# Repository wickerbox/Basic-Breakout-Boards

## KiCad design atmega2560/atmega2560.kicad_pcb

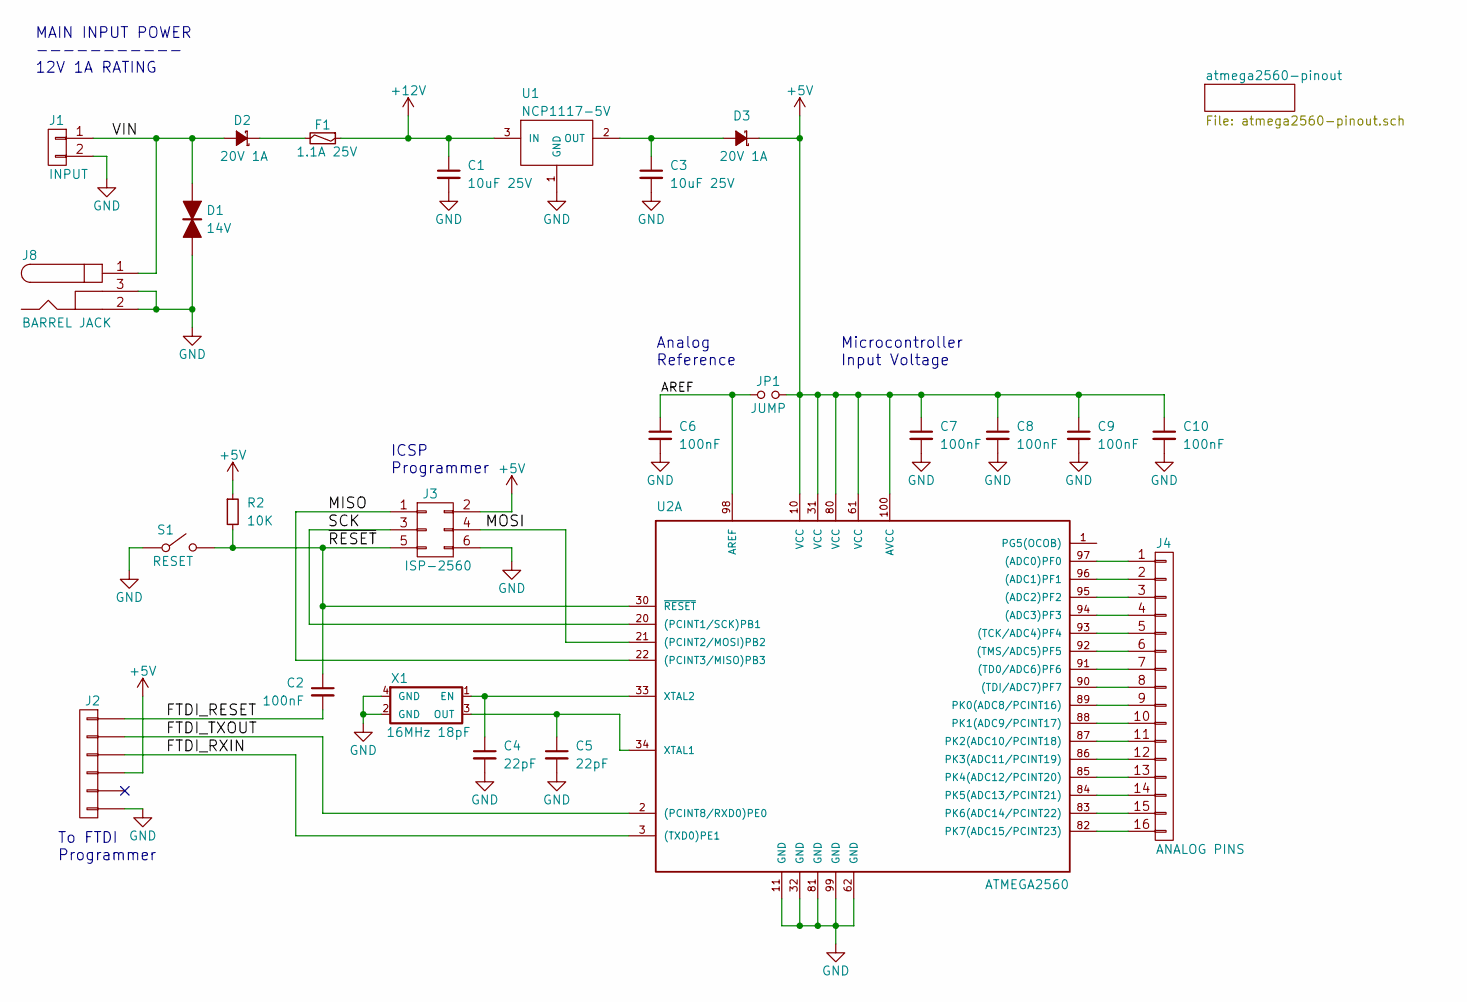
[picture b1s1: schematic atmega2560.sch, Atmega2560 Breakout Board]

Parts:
C1, C3: 10uF 25V; RLC-1210-SMD
C2, C6, C7, C8, C9, C10: 100nF; RLC-0603-SMD
C4, C5: 22pF; RLC-0603-SMD
D1: 14V; DIODE-SMA
D2, D3: 20V 1A; DIODE-SMA
F1: 1.1A 25V; RLC-1812-SMD
J1: INPUT; CONN-ONSHORE-SCREW-GREEN-2PIN-TH
J2: FTDI; CONN-HEADER-STRAIGHT-P2.54MM-1x06
J3: ISP-2560; CONN-HEADER-STRAIGHT-P2.54MM-2x03
J4: ANALOG PINS; CONN-HEADER-STRAIGHT-P2.54MM-1x16
J8: BARREL JACK; CONN-BARREL-JACK-2.5x5.5MM-TH
JP1: JUMP; CONN-HEADER-STRAIGHT-P2.54MM-1x02
R2: 10K; RLC-0805-SMD
S1: RESET; SWITCH-OMRON-MOMENTARY-SMD-B3U-1000P
U1: NCP1117-5V; DPAK
U2: ATMEGA2560; TQFP-100-14x14MM-P0.5MM
X1: 16MHz 18pF; CRYSTAL-CTS-4SMD

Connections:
+5V: C7.1, C8.1, C9.1, C10.1, D3.1 (K), J2.4, J3.2, JP1.2, R2.1, U2.10 (VCC), U2.31 (VCC), U2.61 (VCC), U2.80 (VCC), U2.100 (AVCC)
+12V: C1.1, F1.1, U1.3 (IN)
/AREF: C6.1, JP1.1, U2.98 (AREF)
/FTDI_RESET: C2.2, J2.1
/FTDI_RXIN: J2.3, U2.3 ((TXD0)PE1)
/FTDI_TXOUT: J2.2, U2.2 ((PCINT8/RXD0)PE0)
/MISO: J3.1, U2.22 ((PCINT3/MISO)PB3)
/MOSI: J3.4, U2.21 ((PCINT2/MOSI)PB2)
/SCK: J3.3, U2.20 ((PCINT1/SCK)PB1)
/VIN: D1.1, D2.2 (A), J1.1, J8.1
/~RESET: C2.1, J3.5, R2.2, S1.2, U2.30 (~RESET)
GND: C1.2, C3.2, C4.2, C5.2, C6.2, C7.2, C8.2, C9.2, C10.2, D1.2, J1.2, J2.6, J3.6, J8.2, J8.3, S1.1, U1.1 (GND), U2.11 (GND), U2.32 (GND), U2.62 (GND), U2.81 (GND), U2.99 (GND), X1.2 (GND), X1.4 (GND); also elsewhere on the board
unnamed: C3.1, D3.2 (A), U1.2 (OUT)
unnamed: C4.1, U2.33 (XTAL2), X1.1 (EN)
unnamed: C5.1, U2.34 (XTAL1), X1.3 (OUT)
unnamed: D2.1 (K), F1.2
unnamed: J4.1, U2.97 ((ADC0)PF0)
unnamed: J4.2, U2.96 ((ADC1)PF1)
unnamed: J4.3, U2.95 ((ADC2)PF2)
unnamed: J4.4, U2.94 ((ADC3)PF3)
unnamed: J4.5, U2.93 ((TCK/ADC4)PF4)
unnamed: J4.6, U2.92 ((TMS/ADC5)PF5)
unnamed: J4.7, U2.91 ((TD0/ADC6)PF6)
unnamed: J4.8, U2.90 ((TDI/ADC7)PF7)
unnamed: J4.9, U2.89 (PK0(ADC8/PCINT16))
unnamed: J4.10, U2.88 (PK1(ADC9/PCINT17))
unnamed: J4.11, U2.87 (PK2(ADC10/PCINT18))
unnamed: J4.12, U2.86 (PK3(ADC11/PCINT19))
unnamed: J4.13, U2.85 (PK4(ADC12/PCINT20))
unnamed: J4.14, U2.84 (PK5(ADC13/PCINT21))
unnamed: J4.15, U2.83 (PK6(ADC14/PCINT22))
unnamed: J4.16, U2.82 (PK7(ADC15/PCINT23))
unnamed 47: U2.1 (PG5(OCOB)); also elsewhere on the board

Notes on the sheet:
MAIN INPUT POWER ----------- 12V 1A RATING
To FTDI Programmer
ICSP Programmer
Analog Reference
Microcontroller Input Voltage

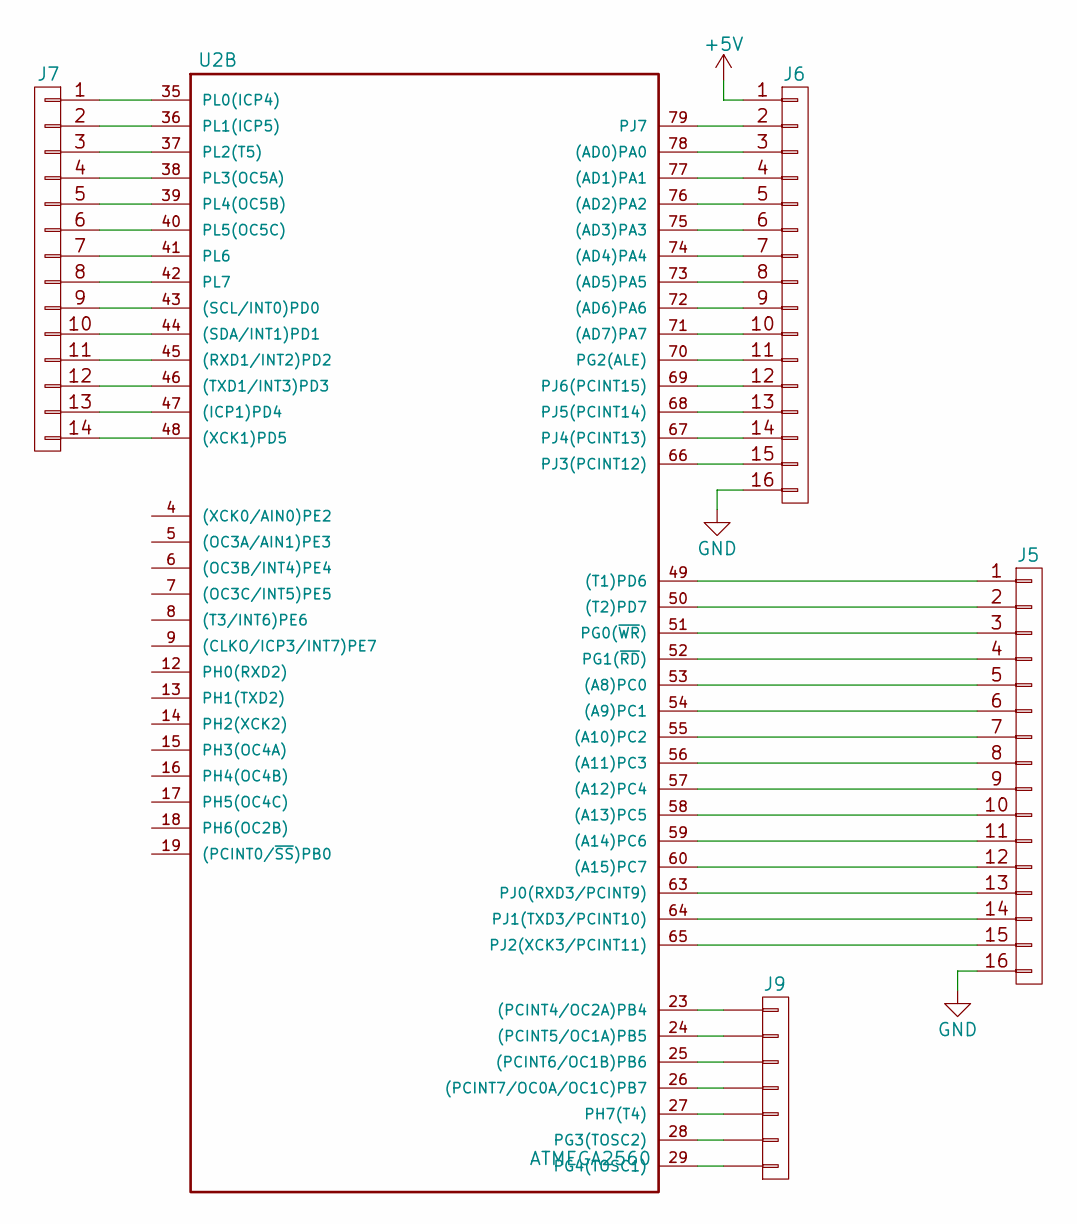
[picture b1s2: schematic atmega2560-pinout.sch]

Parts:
J5, J6: HEADER-FEMALE-16POS-TH-1x16-P0.1IN; CONN-HEADER-STRAIGHT-P2.54MM-1x16
J7: I/O; CONN-HEADER-STRAIGHT-P2.54MM-1x14
J9: HEADER-FEMALE-7POS-TH-1x07-P0.1IN; CONN-HEADER-STRAIGHT-P2.54MM-1x07
U2: ATMEGA2560; TQFP-100-14x14MM-P0.5MM

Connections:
GND: J5.16, J6.16; also elsewhere on the board
unnamed: J5.1, U2.49 ((T1)PD6)
unnamed: J5.2, U2.50 ((T2)PD7)
unnamed: J5.3, U2.51 (PG0(~WR~))
unnamed: J5.4, U2.52 (PG1(~RD~))
unnamed: J5.5, U2.53 ((A8)PC0)
unnamed: J5.6, U2.54 ((A9)PC1)
unnamed: J5.7, U2.55 ((A10)PC2)
unnamed: J5.8, U2.56 ((A11)PC3)
unnamed: J5.9, U2.57 ((A12)PC4)
unnamed: J5.10, U2.58 ((A13)PC5)
unnamed: J5.11, U2.59 ((A14)PC6)
unnamed: J5.12, U2.60 ((A15)PC7)
unnamed: J5.13, U2.63 (PJ0(RXD3/PCINT9))
unnamed: J5.14, U2.64 (PJ1(TXD3/PCINT10))
unnamed: J5.15, U2.65 (PJ2(XCK3/PCINT11))
unnamed 47: J6.1; also elsewhere on the board
unnamed: J6.2, U2.79 (PJ7)
unnamed: J6.3, U2.78 ((AD0)PA0)
unnamed: J6.4, U2.77 ((AD1)PA1)
unnamed: J6.5, U2.76 ((AD2)PA2)
unnamed: J6.6, U2.75 ((AD3)PA3)
unnamed: J6.7, U2.74 ((AD4)PA4)
unnamed: J6.8, U2.73 ((AD5)PA5)
unnamed: J6.9, U2.72 ((AD6)PA6)
unnamed: J6.10, U2.71 ((AD7)PA7)
unnamed: J6.11, U2.70 (PG2(ALE))
unnamed: J6.12, U2.69 (PJ6(PCINT15))
unnamed: J6.13, U2.68 (PJ5(PCINT14))
unnamed: J6.14, U2.67 (PJ4(PCINT13))
unnamed: J6.15, U2.66 (PJ3(PCINT12))
unnamed: J7.1, U2.35 (PL0(ICP4))
unnamed: J7.2, U2.36 (PL1(ICP5))
unnamed: J7.3, U2.37 (PL2(T5))
unnamed: J7.4, U2.38 (PL3(OC5A))
unnamed: J7.5, U2.39 (PL4(OC5B))
unnamed: J7.6, U2.40 (PL5(OC5C))
unnamed: J7.7, U2.41 (PL6)
unnamed: J7.8, U2.42 (PL7)
unnamed: J7.9, U2.43 ((SCL/INT0)PD0)
unnamed: J7.10, U2.44 ((SDA/INT1)PD1)
unnamed: J7.11, U2.45 ((RXD1/INT2)PD2)
unnamed: J7.12, U2.46 ((TXD1/INT3)PD3)
unnamed: J7.13, U2.47 ((ICP1)PD4)
unnamed: J7.14, U2.48 ((XCK1)PD5)
unnamed: J9.1, U2.23 ((PCINT4/OC2A)PB4)
unnamed: J9.2, U2.24 ((PCINT5/OC1A)PB5)
unnamed: J9.3, U2.25 ((PCINT6/OC1B)PB6)
unnamed: J9.4, U2.26 ((PCINT7/OC0A/OC1C)PB7)
unnamed: J9.5, U2.27 (PH7(T4))
unnamed: J9.6, U2.28 (PG3(TOSC2))
unnamed: J9.7, U2.29 (PG4(TOSC1))

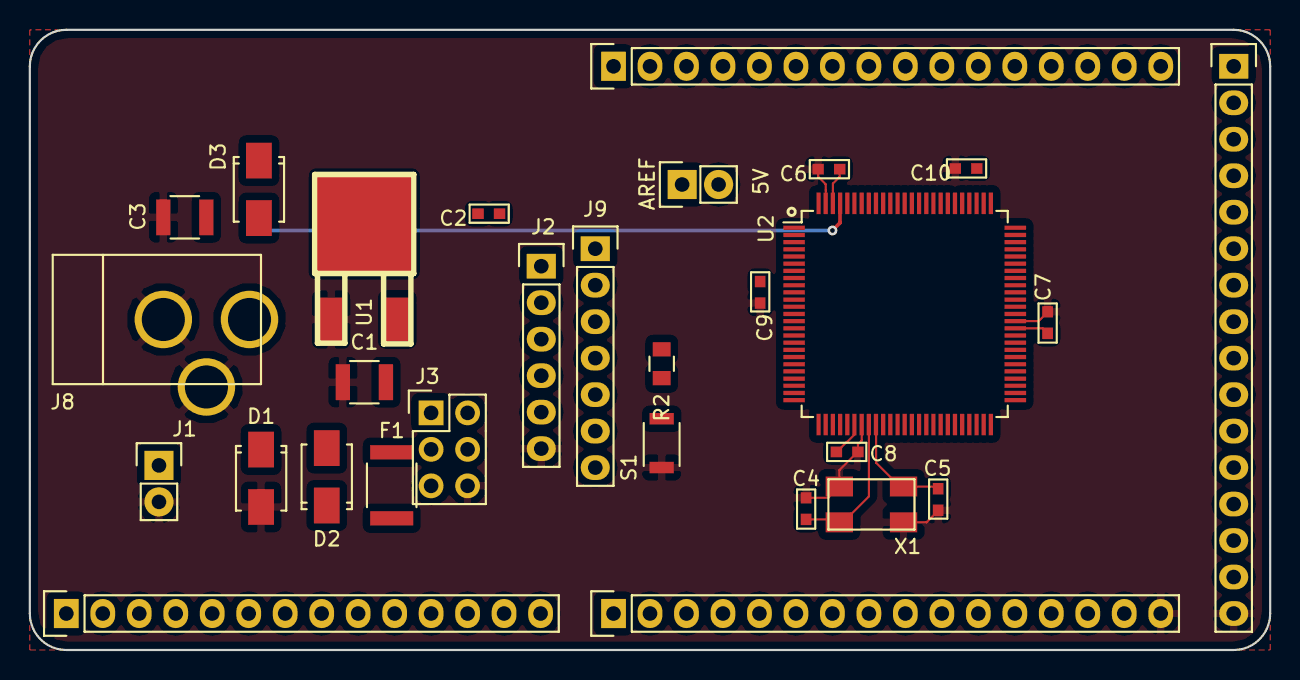
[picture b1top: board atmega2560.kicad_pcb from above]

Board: 2 copper layers, 86.4 x 43.2 mm, 29 parts (0 on the bottom side), 83 nets.

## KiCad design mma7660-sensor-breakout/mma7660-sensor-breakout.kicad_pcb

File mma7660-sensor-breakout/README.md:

<!--- start title --->
# MMA7660 3-axis Accelerometer Breakout v1.1

A breadboard-compatible breakout board for the MMA7660 accelerometer.

Updated: 7 March 2017

- Author: Jenner Hanni
- Website: http://wickerbox.net
- Company: Wickerbox Electronics
- License: CERN Open Hardware License v1.2

<!--- end title --->
This is a breadboard-compatible breakout board for the MMA7660 accelerometer.

The project is released as open hardware under the CERN v1.2 Open Hardware license.

The I2C lines have 1K pull-up resistors.

You can order a set of three bare boards for $1.25 <a href="https://oshpark.com/shared_projects/YDCCxiCM">from OSH Park</a>.

### Bill of Materials

<!--- bom start --->
|Ref|Qty|Description|Digikey PN|
|---|---|-----------|------|
|C2 C1|2|CAP CER 0.1UF 25V X7R 0805|1276-1099-1-ND|
|J1|1|HEADER MALE 5POS TH 1x05 0.1”|952-1902-ND|
|R1 R2|2|RES SMD 1K OHM 1% 1/10W 0603|1276-3484-1-ND|
|U1|1|IC ACCELEROMETER 3X3 DGTL 10-DFN|MMA7660FCT-ND|
<!--- bom end --->

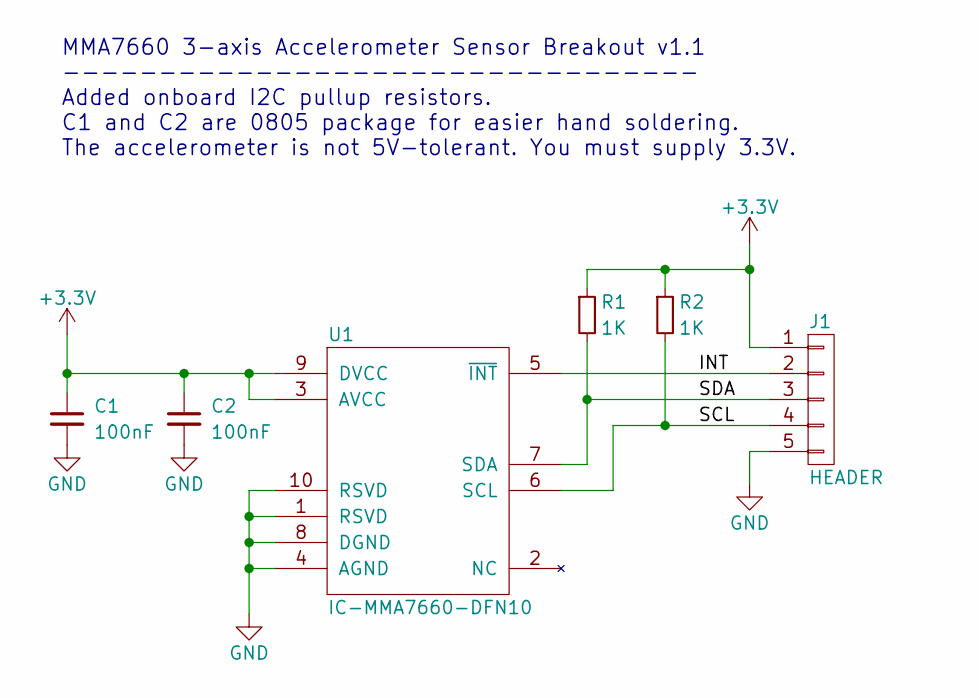
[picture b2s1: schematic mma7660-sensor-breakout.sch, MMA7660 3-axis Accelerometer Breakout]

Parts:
C1, C2: 100nF; RLC-0805
J1: HEADER; CONN-HEADER-STRAIGHT-P2.54MM-1x05
R1, R2: 1K; RLC-0603-SMD
U1: IC-MMA7660-DFN10; DFN-10-1EP-3x3MM-P0.5MM

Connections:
+3V3: C1.1, C2.1, J1.1, R1.1, R2.1, U1.3 (AVCC), U1.9 (DVCC)
/INT: J1.2, U1.5 (~INT)
/SCL: J1.4, R2.2, U1.6 (SCL)
/SDA: J1.3, R1.2, U1.7 (SDA)
GND: C1.2, C2.2, J1.5, U1.1 (RSVD), U1.4 (AGND), U1.8 (DGND), U1.10 (RSVD)

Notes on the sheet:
MMA7660 3-axis Accelerometer Sensor Breakout v1.1 --------------------------------- Added onboard I2C pullup resistors. C1 and C2 are 0805 package for easier hand soldering. The accelerometer is not 5V-tolerant. You must supply 3.3V.

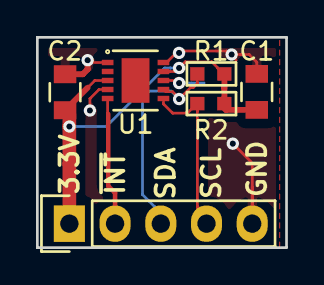
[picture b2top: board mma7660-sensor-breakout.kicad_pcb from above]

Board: 2 copper layers, 13.8 x 11.7 mm, 6 parts (0 on the bottom side), 5 nets.

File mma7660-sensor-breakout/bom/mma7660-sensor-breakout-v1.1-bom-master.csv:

Ref,Qty,Value,Footprint,Footprint Library,Symbol,Symbol Library,Datasheet,Package,MF_Name,MF_PN,S1_Name,S1_PN,Description,Verified
C2 C1,2,100nF,RLC-0805,Wickerlib,CAP-CER-0.1UF-25V-X7R-0805,wickerlib,http://www.samsungsem.com/kr/front/downloadcms.do?path=/kr/s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,Samsung,CL21B104KACNNNC,Digikey,1276-1099-1-ND,CAP CER 0.1UF 25V X7R 0805
J1,1,HEADER,CONN-HEADER-STRAIGHT-P2.54MM-1x05,Wickerlib,HEADER-MALE-5POS-TH-1x05-P0.1IN,wickerlib,https://cdn.harwin.com/pdfs/60page140.pdf,Pin_Header_Straight_1x05,Harwin,M20-9992046,Digikey,952-1902-ND,HEADER MALE 5POS TH 1x05 0.1”,Not Verified
R1 R2,2,1K,RLC-0603-SMD,Wickerlib,RES-1K-1%-1/10W-0603,wickerlib,http://media.digikey.com/pdf/Data%20Sheets/Samsung%20PDFs/RC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,Samsung,RC1608F102CS,Digikey,1276-3484-1-ND,RES SMD 1K OHM 1% 1/10W 0603
U1,1,IC-MMA7660-DFN10,DFN-10-1EP-3x3MM-P0.5MM,Wickerlib,IC-MMA7660-DFN10,wickerlib,http://cache.freescale.com/files/sensors/doc/data_sheet/MMA7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,Freescale NXP,MMA7660FCT,Digikey,MMA7660FCT-ND,IC ACCELEROMETER 3X3 DGTL 10-DFN

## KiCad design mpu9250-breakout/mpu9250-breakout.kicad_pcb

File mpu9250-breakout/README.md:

<!--- start title --->
# MPU9250 9-axis IMU Breakout Board v1.0
A breadboard-compatible breakout board for the MPU9250 9-axis IMU sensor.

Updated: 01 Jan 2017

Author: Jenner Hanni
Website: http://wickerbox.net
Company: Wickerbox Electronics
License: CERN Open Hardware License v1.2

<!--- end title --->

There are two boards in the same file, one in SPI mode and one in I2C mode. 

### Bill of Materials

<!--- bom start --->
|Ref|Qty|Description|Digikey PN|
|---|---|-----------|------|
|C1 C4|2|CAP CER 10000PF 50V X7R 0402|311-1349-1-ND|
|C3 C2 C6 C5|4|CAP CER 0.1UF 16V X7R 0402|1276-1001-1-ND|
|J1 J2 J4 J3|4|HEADER MALE 5POS TH 1x05 0.1”|952-1902-ND|
|JP1 JP2|2|SHUNT JUMPER 0.1IN BLACK GOLD|3M9580-ND|
|U1 U2|2|GYRO/ACCEL/MAG 9-AXIS I2C/SPI QFN24 MPU9150|1428-1019-1-ND|
<!--- bom end --->
\pagebreak

### Assembly Diagrams

### Board Preview

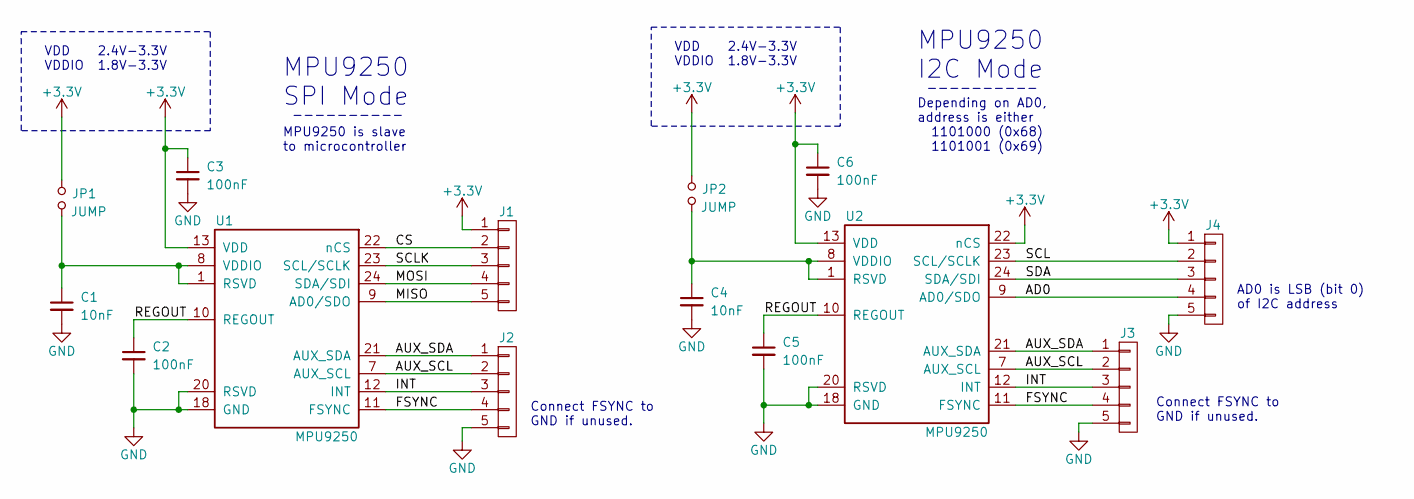
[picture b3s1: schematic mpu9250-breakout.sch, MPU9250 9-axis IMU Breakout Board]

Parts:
C1, C4: 10nF; RLC-0402-SMD
C2, C3, C5, C6: 100nF; RLC-0402-SMD
J1, J2, J3, J4: HEADER; CONN-HEADER-STRAIGHT-P2.54MM-1x05
JP1, JP2: JUMP; CONN-HEADER-STRAIGHT-P2.54MM-1x02
U1, U2: MPU9250; QFN-24_3x3MM_P0.4MM

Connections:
+3V3: C3.1, C6.1, J1.1, J4.1, JP1.2, JP2.2, U1.13 (VDD), U2.13 (VDD), U2.22 (nCS)
/AD0: J4.4, U2.9 (AD0/SDO)
/AUX_SCL: J2.2, J3.2, U1.7 (AUX_SCL), U2.7 (AUX_SCL)
/AUX_SDA: J2.1, J3.1, U1.21 (AUX_SDA), U2.21 (AUX_SDA)
/CS: J1.2, U1.22 (nCS)
/FSYNC: J2.4, J3.4, U1.11 (FSYNC), U2.11 (FSYNC)
/INT: J2.3, J3.3, U1.12 (INT), U2.12 (INT)
/MISO: J1.5, U1.9 (AD0/SDO)
/MOSI: J1.4, U1.24 (SDA/SDI)
/REGOUT: C2.1, C5.1, U1.10 (REGOUT), U2.10 (REGOUT)
/SCL: J4.2, U2.23 (SCL/SCLK)
/SCLK: J1.3, U1.23 (SCL/SCLK)
/SDA: J4.3, U2.24 (SDA/SDI)
GND: C1.2, C2.2, C3.2, C4.2, C5.2, C6.2, J2.5, J3.5, J4.5, U1.18 (GND), U1.20 (RSVD), U2.18 (GND), U2.20 (RSVD)
unnamed: C1.1, JP1.1, U1.1 (RSVD), U1.8 (VDDIO)
unnamed: C4.1, JP2.1, U2.1 (RSVD), U2.8 (VDDIO)

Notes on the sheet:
MPU9250 SPI Mode
MPU9250 is slave to microcontroller
----------
VDD 2.4V-3.3V VDDIO 1.8V-3.3V
Connect FSYNC to GND if unused.
MPU9250 I2C Mode
AD0 is LSB (bit 0) of I2C address
Depending on AD0, address is either 1101000 (0x68) 1101001 (0x69)

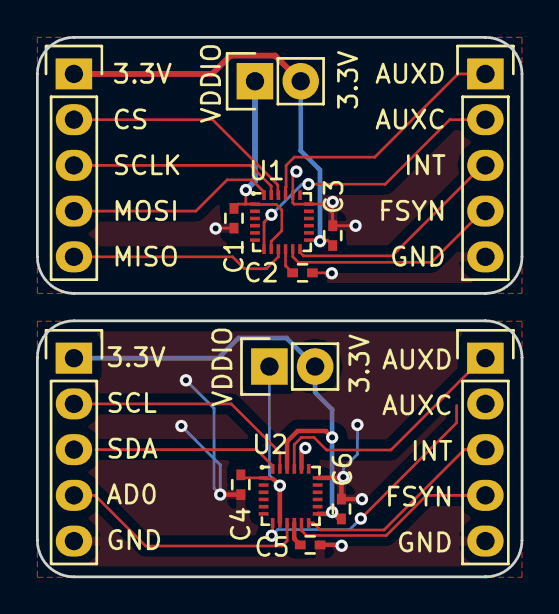
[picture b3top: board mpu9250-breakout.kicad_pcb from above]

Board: 2 copper layers, 26.9 x 30.0 mm, 14 parts (0 on the bottom side), 16 nets.

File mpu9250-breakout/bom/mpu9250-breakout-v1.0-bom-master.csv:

Ref,Qty,Value,Footprint,Footprint Library,Symbol,Symbol Library,Datasheet,Description,MF_Name,MF_PN,S1_Name,S1_PN
C1 C4,2,10nF,RLC-0402-SMD,Wickerlib,CAP-CER-10NF-50V-X7R-0402,wickerlib,http://www.digikey.com/en/ptm/k/kemet/capacitor-basics---typ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,CAP CER 10000PF 50V X7R 0402,Yageo,CC0402KRX7R9BB103,Digikey,311-1349-1-ND
C3 C2 C6 C5,4,100nF,RLC-0402-SMD,Wickerlib,CAP-CER-100NF-16V-X7R-0402,wickerlib,http://www.samsungsem.com/kr/support/product-search/mlcc/CL0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,CAP CER 0.1UF 16V X7R 0402,Samsung,CL05B104KO5NNNC,Digikey,1276-1001-1-ND
J1 J2 J4 J3,4,HEADER,CONN-HEADER-STRAIGHT-P2.54MM-1x05,Wickerlib,HEADER-MALE-5POS-TH-1x05-P0.1IN,wickerlib,https://cdn.harwin.com/pdfs/60page140.pdf,HEADER MALE 5POS TH 1x05 0.1”,Harwin,M20-9992046,Digikey,952-1902-ND
JP1 JP2,2,JUMP,CONN-HEADER-STRAIGHT-P2.54MM-1x02,Wickerlib,SHUNT-JUMPER-2PIN-P0.1IN,wickerlib,,SHUNT JUMPER 0.1IN BLACK GOLD,3M,969102-0000-DA,Digikey,3M9580-ND
U1 U2,2,MPU9250,QFN-24_3x3MM_P0.4MM,Wickerlib,IC-9-AXIS-IMU-MPU9250-QFN24,wickerlib,https://store.invensense.com/datasheets/invensense/MPU9250RE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,GYRO/ACCEL/MAG 9-AXIS I2C/SPI QFN24 MPU9150,Invensense,MPU-9250,Digikey,1428-1019-1-ND

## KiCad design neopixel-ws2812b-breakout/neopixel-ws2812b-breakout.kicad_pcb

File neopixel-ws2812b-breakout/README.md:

<!--- start title --->
# Neopixel WS2812B Breakout Board v1.1
This is a breadboard-compatible breakout board for a WS2812B or 5050-compatible RGB "Neopixel" LED.

Updated: 7 Feb 2017

- Author: Jenner Hanni
- Website: http://wickerbox.net
- Company: Wickerbox Electronics
- License: CERN Open Hardware License v1.2

<!--- end title --->

It must be used with 5V, and includes a 470-ohm resistor on the input DI line to protect against voltage spikes. The project is released as open hardware under the CERN v1.2 Open Hardware license.

You can order a set of three bare boards for $1.20 <a href="https://oshpark.com/shared_projects/DExj7dKh">from OSH Park</a>.

<!--- bom start --->
|Ref|Qty|Description|Digikey PN|
|---|---|-----------|------|
|J2 J1|2|HEADER MALE 2POS TH 1x02 0.1”|952-2262-ND|
|LED1|1|LED RGB WS2812B W/DVR 4SMD|1528-1104-ND|
|R1|1|RES SMD 470 OHM 5% 1/4W 0603|RHM470DCT-ND|

<!--- bom end --->

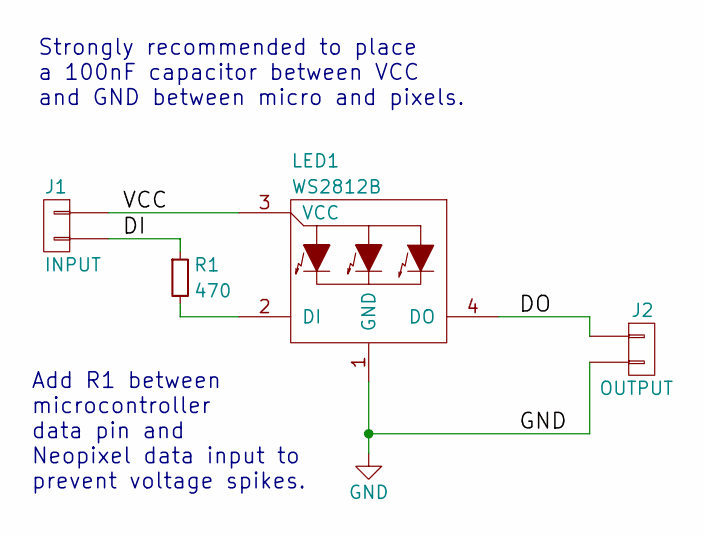
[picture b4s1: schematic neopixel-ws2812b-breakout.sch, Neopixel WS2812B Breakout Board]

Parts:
J1: INPUT; CONN-HEADER-STRAIGHT-P2.54MM-1x02
J2: OUTPUT; CONN-HEADER-STRAIGHT-P2.54MM-1x02
LED1: WS2812B; LED-RGB-5050-SMD
R1: 470; RLC-0603-SMD

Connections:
/DI: J1.2, R1.1
/DO: J2.1, LED1.4 (DO)
/VCC: J1.1, LED1.3 (VCC)
GND: J2.2, LED1.1 (GND)
unnamed: LED1.2 (DI), R1.2

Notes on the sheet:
Add R1 between microcontroller data pin and Neopixel data input to prevent voltage spikes.
Strongly recommended to place a 100nF capacitor between VCC and GND between micro and pixels.

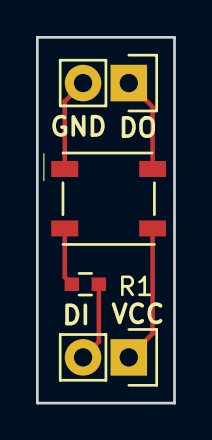
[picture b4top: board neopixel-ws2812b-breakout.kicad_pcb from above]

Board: 2 copper layers, 7.6 x 20.3 mm, 4 parts (0 on the bottom side), 5 nets.

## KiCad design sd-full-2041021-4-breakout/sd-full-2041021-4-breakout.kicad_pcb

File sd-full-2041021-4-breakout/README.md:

<!--- start title --->
# Full-size SD Connector (2041021-4) Breakout Board vv1.0
Breadboard- and 3V/5V-compatible SD breakout board to test the full-size SD card footprint.

Updated: 4 Jan 2017

- Author: Jenner Hanni
- Website: http://wickerbox.net
- Company: Wickerbox Electronics
- License: CERN Open Hardware License v1.2

<!--- end title --->

### Bill of Materials

<!--- bom start --->
|Ref|Qty|Description|Digikey PN|
|---|---|-----------|------|
|C2 C3|2|CAP CER 0.1UF 100V X7R 0603|490-3285-1-ND|
|C4 C1|2|CAP CER 1UF 25V X7R 0603|587-2984-1-ND|
|J1|1|HEADER MALE 6POS TH 1x06 0.1”|952-1902-ND|
|J2|1|CONN SD CARD PUSH-PULL R/A SMD|A101492CT-ND|
|U1|1|IC REG LDO 3.3V 0.15A SOT353|576-3193-1-ND|
|U2|1|IC VOLT-LEVEL TRANSLATOR TXB0104 SOIC14|296-21928-1-ND|

<!--- bom end --->

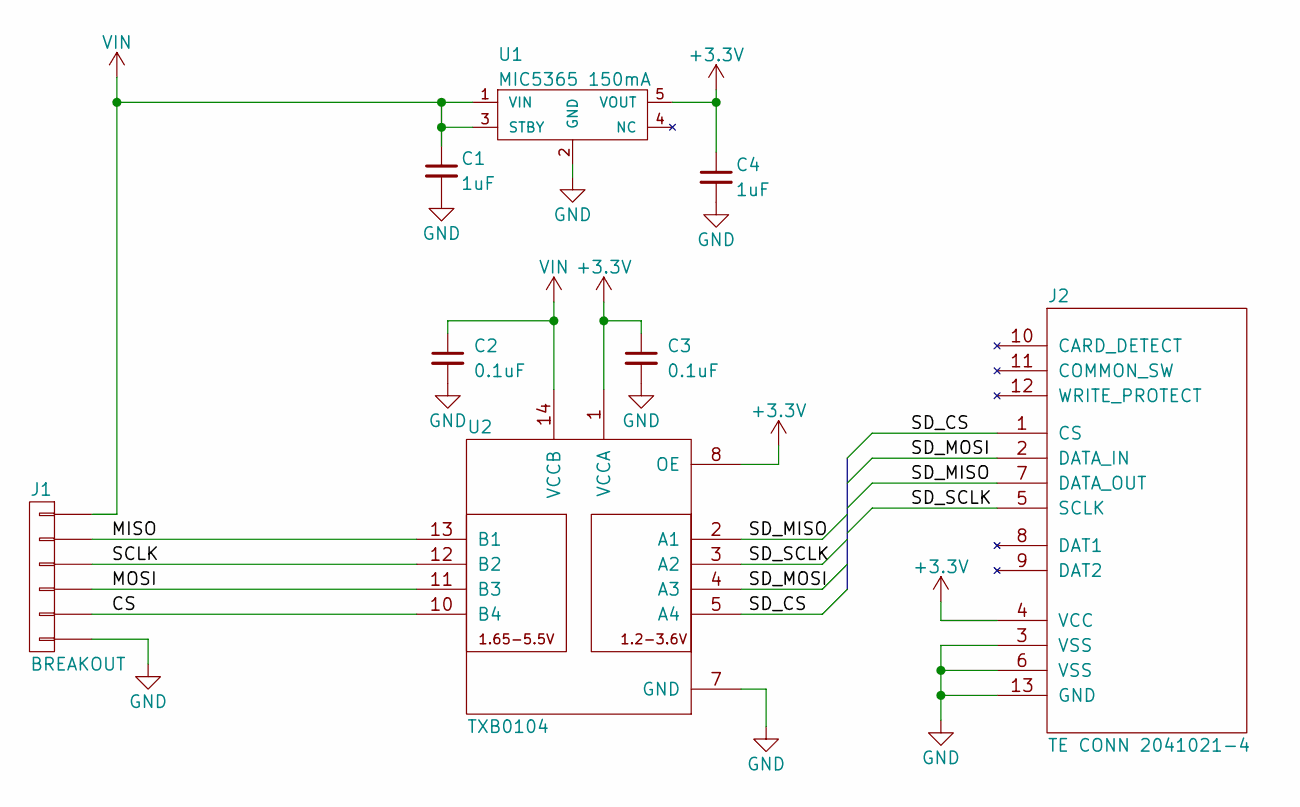
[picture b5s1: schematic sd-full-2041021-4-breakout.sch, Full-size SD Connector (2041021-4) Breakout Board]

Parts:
C1, C4: 1uF; RLC-0603-SMD
C2, C3: 0.1uF; RLC-0603-SMD
J1: BREAKOUT; CONN-HEADER-STRAIGHT-P2.54MM-1x06
J2: TE CONN 2041021-4; CONN-SD-FULL-TECONN-2041021-4
U1: MIC5365 150mA; SOT-353
U2: TXB0104; SOIC-14-3.9x8.7MM-P1.27MM

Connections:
+3V3: C3.1, C4.1, J2.4 (VCC), U1.5 (VOUT), U2.1 (VCCA), U2.8 (OE)
/CS: J1.5, U2.10 (B4)
/MISO: J1.2, U2.13 (B1)
/MOSI: J1.4, U2.11 (B3)
/SCLK: J1.3, U2.12 (B2)
/SD_CS: J2.1 (CS), U2.5 (A4)
/SD_MISO: J2.7 (DATA_OUT), U2.2 (A1)
/SD_MOSI: J2.2 (DATA_IN), U2.4 (A3)
/SD_SCLK: J2.5 (SCLK), U2.3 (A2)
GND: C1.2, C2.2, C3.2, C4.2, J1.6, J2.3 (VSS), J2.6 (VSS), J2.13 (GND), U1.2 (GND), U2.7 (GND)
VIN: C1.1, C2.1, J1.1, U1.1 (VIN), U1.3 (STBY), U2.14 (VCCB)

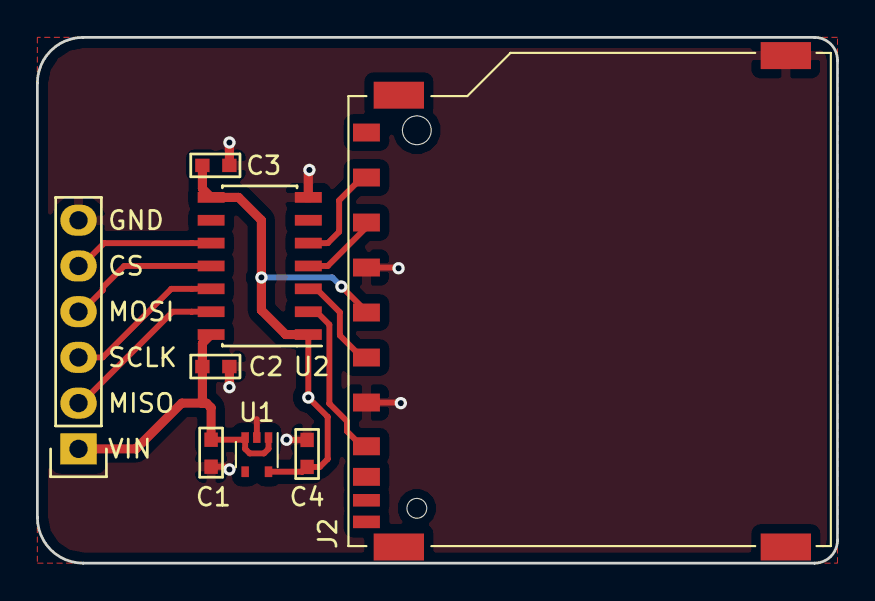
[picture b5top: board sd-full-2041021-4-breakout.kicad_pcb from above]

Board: 2 copper layers, 44.5 x 29.2 mm, 8 parts (0 on the bottom side), 11 nets.

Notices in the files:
mma7660-sensor-breakout/mma7660-sensor-breakout.sch:
Released under the CERN Open Hardware License v1.2
